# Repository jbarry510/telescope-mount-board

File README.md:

# telescope-mount-board
Printed circuit board design for a stepper motor driven telescope mount.

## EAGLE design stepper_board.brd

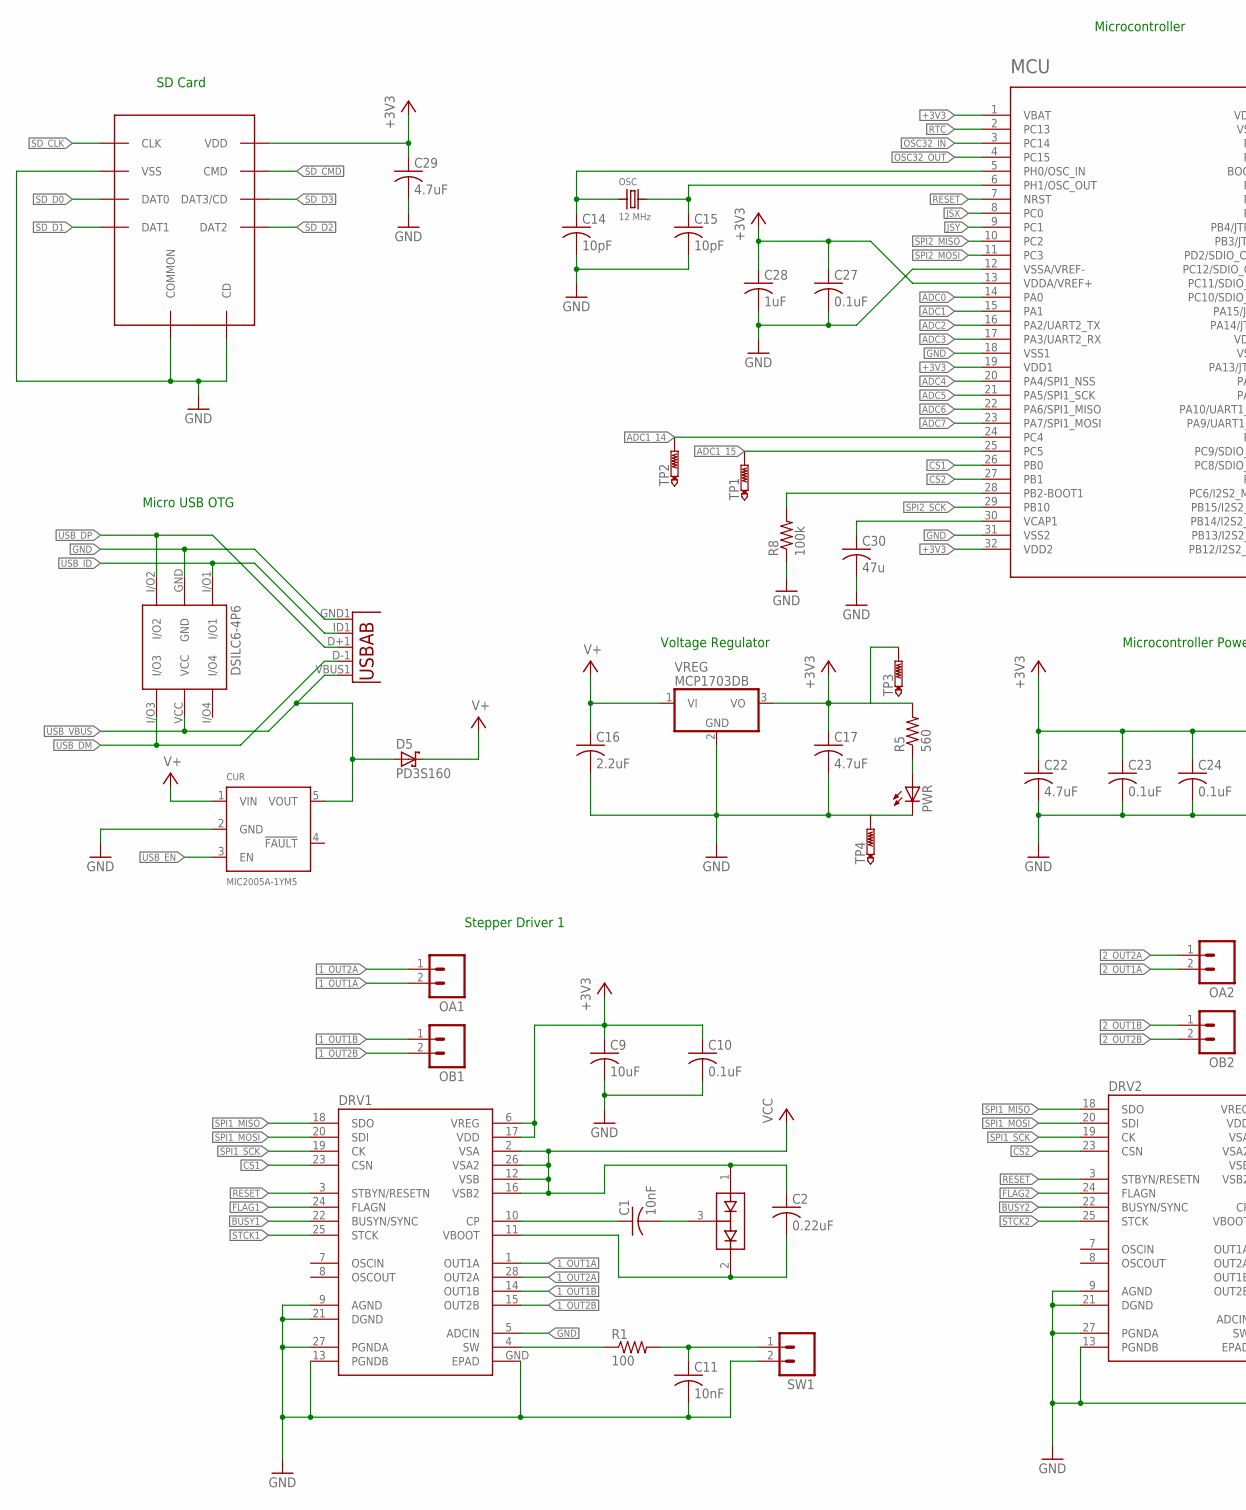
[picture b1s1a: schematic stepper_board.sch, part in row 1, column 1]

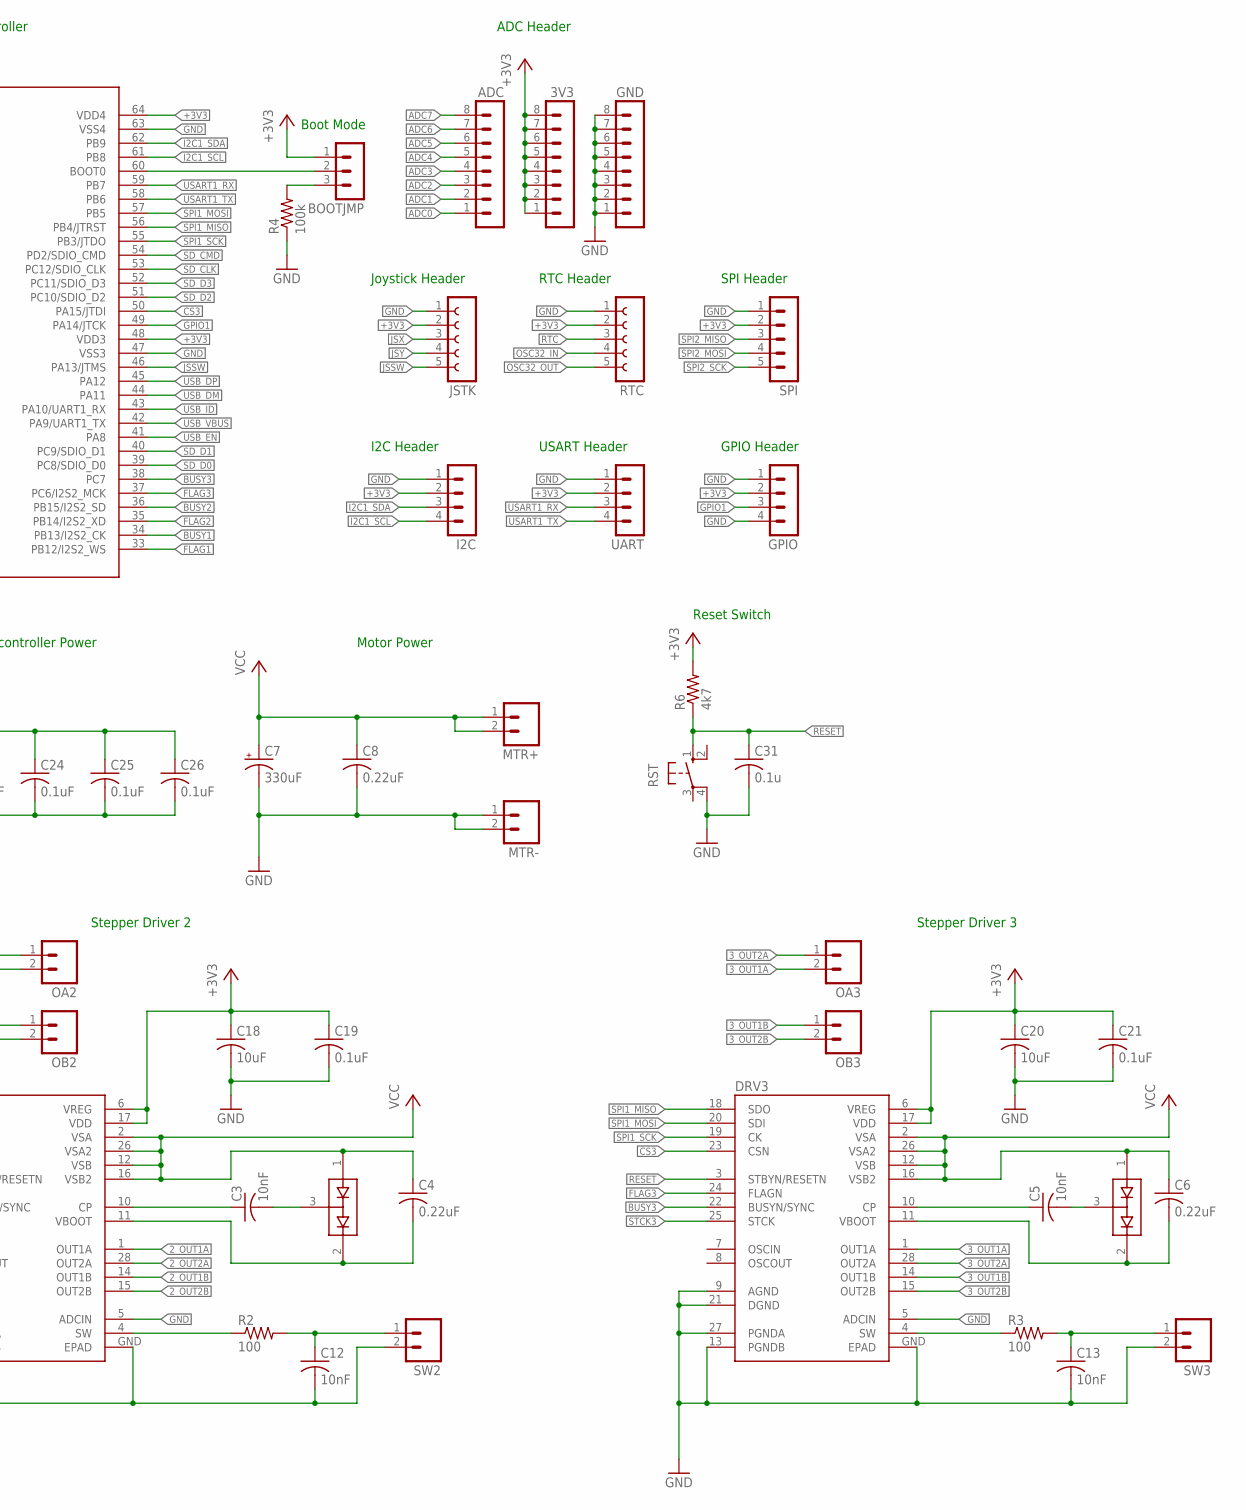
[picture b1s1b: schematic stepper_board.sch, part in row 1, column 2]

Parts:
3V3: MA08-1
ADC: MA08-1
BOOTJMP: MA03-1
C1, C3, C5, C11, C12, C13: 10nF; C0805
C2, C4, C6, C8: 0.22uF; C0805
C7: 330uF; UD-10X10_NICHICON
C9, C18, C20: 10uF; C0805
C10, C19, C21, C23, C24, C25, C26, C27: 0.1uF; C0805
C14, C15: 10pF; C0805
C16: 2.2uF; C0805
C17, C22, C29: 4.7uF; C0805
C28: 1uF; C0805
C30: 47u; C0805
C31: 0.1u; C0805
CUR: MIC2005A-1YM5; SOT23-5
D1, D2, D3: BAV99; SOT23
D5: PD3S160; POWERDI323
DRV1, DRV2, DRV3: L6470; HTSSOP28-NOPAD
ESD: DSILC6-4P6; SOT-666
GND: MA08-1
GPIO: MA04-1
I2C: MA04-1
JSTK: FE05-1
MCU: STM32F411RE; TQFP64
MICROSD: SCHA5B0200
MTR+: M02; 02P
MTR-: M02; 02P
OA1, OA2, OA3: M02; 02P
OB1, OB2, OB3: M02; 02P
OSC: 12 MHz; 3.2X2.5MM
PWR: LEDCHIP-LED0805; CHIP-LED0805
R1, R2, R3: 100; R0805
R4, R8: 100k; R0805
R5: 560; R0805
R6: 4k7; R0805
RST: 10-XX; B3F-10XX
RTC: FE05-1
SPI: MA05-1
SW1, SW2, SW3: M02; 02P
TP1, TP2, TP3, TP4: PTR1B1,27; B1,27
UART: MA04-1
USB: USB""; USB-MICRO-SMD
VREG: MCP1703DB; SOT223

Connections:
1_OUT1A: DRV1.1 (OUT1A), OA1.2
1_OUT1B: DRV1.14 (OUT1B), OB1.1
1_OUT2A: DRV1.28 (OUT2A), OA1.1
1_OUT2B: DRV1.15 (OUT2B), OB1.2
2_OUT1A: DRV2.1 (OUT1A), OA2.2
2_OUT1B: DRV2.14 (OUT1B), OB2.1
2_OUT2A: DRV2.28 (OUT2A), OA2.1
2_OUT2B: DRV2.15 (OUT2B), OB2.2
3_OUT1A: DRV3.1 (OUT1A), OA3.2
3_OUT1B: DRV3.14 (OUT1B), OB3.1
3_OUT2A: DRV3.28 (OUT2A), OA3.1
3_OUT2B: DRV3.15 (OUT2B), OB3.2
+3V3: 3V3.1, 3V3.2, 3V3.3, 3V3.4, 3V3.5, 3V3.6, 3V3.7, 3V3.8, BOOTJMP.1, C9.1, C10.1, C17.1, C18.1, C19.1, C20.1, C21.1, C22.1, C23.1, C24.1, C25.1, C26.1, C27.1, C28.1, C29.1, DRV1.6 (VREG), DRV1.17 (VDD), DRV2.6 (VREG), DRV2.17 (VDD), DRV3.6 (VREG), DRV3.17 (VDD), GPIO.2, I2C.2, JSTK.2, MCU.1 (VBAT), MCU.13 (VDDA/VREF+), MCU.19 (VDD1), MCU.32 (VDD2), MCU.48 (VDD3), MCU.64 (VDD4), MICROSD.VDD, R5.2, R6.2, RTC.2, SPI.2, TP3.TP, UART.2, VREG.3 (VO)
ADC0: ADC.1, MCU.14 (PA0)
ADC1: ADC.2, MCU.15 (PA1)
ADC1_14: MCU.24 (PC4), TP2.TP
ADC1_15: MCU.25 (PC5), TP1.TP
ADC2: ADC.3, MCU.16 (PA2/UART2_TX)
ADC3: ADC.4, MCU.17 (PA3/UART2_RX)
ADC4: ADC.5, MCU.20 (PA4/SPI1_NSS)
ADC5: ADC.6, MCU.21 (PA5/SPI1_SCK)
ADC6: ADC.7, MCU.22 (PA6/SPI1_MISO)
ADC7: ADC.8, MCU.23 (PA7/SPI1_MOSI)
BUSY1: DRV1.22 (BUSYN/SYNC), MCU.34 (PB13/I2S2_CK)
BUSY2: DRV2.22 (BUSYN/SYNC), MCU.36 (PB15/I2S2_SD)
BUSY3: DRV3.22 (BUSYN/SYNC), MCU.38 (PC7)
CS1: DRV1.23 (CSN), MCU.26 (PB0)
CS2: DRV2.23 (CSN), MCU.27 (PB1)
CS3: DRV3.23 (CSN), MCU.50 (PA15/JTDI)
FLAG1: DRV1.24 (FLAGN), MCU.33 (PB12/I2S2_WS)
FLAG2: DRV2.24 (FLAGN), MCU.35 (PB14/I2S2_XD)
FLAG3: DRV3.24 (FLAGN), MCU.37 (PC6/I2S2_MCK)
GND: C7.-, C8.2, C9.2, C10.2, C11.2, C12.2, C13.2, C14.2, C15.2, C16.2, C17.2, C18.2, C19.2, C20.2, C21.2, C22.2, C23.2, C24.2, C25.2, C26.2, C27.2, C28.2, C29.2, C30.2, C31.2, CUR.2 (GND), DRV1.5 (ADCIN), DRV1.9 (AGND), DRV1.13 (PGNDB), DRV1.21 (DGND), DRV1.27 (PGNDA), DRV1.GND (EPAD), DRV2.5 (ADCIN), DRV2.9 (AGND), DRV2.13 (PGNDB), DRV2.21 (DGND), DRV2.27 (PGNDA), DRV2.GND (EPAD), DRV3.5 (ADCIN), DRV3.9 (AGND), DRV3.13 (PGNDB), DRV3.21 (DGND), DRV3.27 (PGNDA), DRV3.GND (EPAD), ESD.GND, GND.1, GND.2, GND.3, GND.4, GND.5, GND.6, GND.7, GND.8, GPIO.1, GPIO.4, I2C.1, JSTK.1, MCU.12 (VSSA/VREF-), MCU.18 (VSS1), MCU.31 (VSS2), MCU.47 (VSS3), MCU.63 (VSS4), MICROSD.CD_SW (CD), MICROSD.COMMON, MICROSD.VSS, MTR-.1, MTR-.2, PWR.C, R4.1, R8.1, RST.4 (P1), RTC.1, SPI.1, SW1.2, SW2.2, SW3.2, TP4.TP, UART.1, USB.GND1 (GND), VREG.2 (GND)
GPIO1: GPIO.3, MCU.49 (PA14/JTCK)
I2C1_SCL: I2C.4, MCU.61 (PB8)
I2C1_SDA: I2C.3, MCU.62 (PB9)
JSSW: JSTK.5, MCU.46 (PA13/JTMS)
JSX: JSTK.3, MCU.8 (PC0)
JSY: JSTK.4, MCU.9 (PC1)
unnamed: C1.1, DRV1.10 (CP)
unnamed: C1.2, D1.3 (COM)
unnamed: C2.2, D1.2 (C2), DRV1.11 (VBOOT)
unnamed: C3.1, DRV2.10 (CP)
unnamed: C3.2, D2.3 (COM)
unnamed: C4.2, D2.2 (C2), DRV2.11 (VBOOT)
unnamed: DRV1.4 (SW), R1.1
unnamed: C5.1, DRV3.10 (CP)
unnamed: C5.2, D3.3 (COM)
unnamed: C6.2, D3.2 (C2), DRV3.11 (VBOOT)
unnamed: C11.1, R1.2, SW1.1
unnamed: DRV2.4 (SW), R2.1
unnamed: C12.1, R2.2, SW2.1
unnamed: DRV3.4 (SW), R3.1
unnamed: C13.1, R3.2, SW3.1
unnamed: C14.1, MCU.5 (PH0/OSC_IN), OSC.1
unnamed: C15.1, MCU.6 (PH1/OSC_OUT), OSC.3 (2)
unnamed: BOOTJMP.2, MCU.60 (BOOT0)
unnamed: BOOTJMP.3, R4.2
unnamed: PWR.A, R5.1
unnamed: C30.1, MCU.30 (VCAP1)
unnamed: MCU.28 (PB2-BOOT1), R8.2
OSC32_IN: MCU.3 (PC14), RTC.4
OSC32_OUT: MCU.4 (PC15), RTC.5
RESET: C31.1, DRV1.3 (STBYN/RESETN), DRV2.3 (STBYN/RESETN), DRV3.3 (STBYN/RESETN), MCU.7 (NRST), R6.1, RST.1 (S)
RTC: MCU.2 (PC13), RTC.3
SD_CLK: MCU.53 (PC12/SDIO_CLK), MICROSD.CLK
SD_CMD: MCU.54 (PD2/SDIO_CMD), MICROSD.CMD
SD_D0: MCU.39 (PC8/SDIO_D0), MICROSD.DAT0
SD_D1: MCU.40 (PC9/SDIO_D1), MICROSD.DAT1
SD_D2: MCU.51 (PC10/SDIO_D2), MICROSD.DAT2
SD_D3: MCU.52 (PC11/SDIO_D3), MICROSD.DAT3/CD
SPI1_MISO: DRV1.18 (SDO), DRV2.18 (SDO), DRV3.18 (SDO), MCU.56 (PB4/JTRST)
SPI1_MOSI: DRV1.20 (SDI), DRV2.20 (SDI), DRV3.20 (SDI), MCU.57 (PB5)
SPI1_SCK: DRV1.19 (CK), DRV2.19 (CK), DRV3.19 (CK), MCU.55 (PB3/JTDO)
SPI2_MISO: MCU.10 (PC2), SPI.3
SPI2_MOSI: MCU.11 (PC3), SPI.4
SPI2_SCK: MCU.29 (PB10), SPI.5
STCK1: DRV1.25 (STCK)
STCK2: DRV2.25 (STCK)
STCK3: DRV3.25 (STCK)
USART1_RX: MCU.59 (PB7), UART.3
USART1_TX: MCU.58 (PB6), UART.4
USB_DM: ESD.I/O3, MCU.44 (PA11), USB.D-1 (D-)
USB_DP: ESD.I/O2, MCU.45 (PA12), USB.D+1 (D+)
USB_EN: CUR.3 (EN), MCU.41 (PA8)
USB_ID: ESD.I/O1, MCU.43 (PA10/UART1_RX), USB.ID1 (USBID)
USB_VBUS: CUR.5 (VOUT), D5.A, ESD.VCC, MCU.42 (PA9/UART1_TX), USB.VBUS1 (VBUS)
V+: C16.1, CUR.1 (VIN), D5.C, VREG.1 (VI)
VCC: C2.1, C4.1, C6.1, C7.+, C8.1, D1.1 (A1), D2.1 (A1), D3.1 (A1), DRV1.2 (VSA), DRV1.12 (VSB), DRV1.16 (VSB2), DRV1.26 (VSA2), DRV2.2 (VSA), DRV2.12 (VSB), DRV2.16 (VSB2), DRV2.26 (VSA2), DRV3.2 (VSA), DRV3.12 (VSB), DRV3.16 (VSB2), DRV3.26 (VSA2), MTR+.1, MTR+.2

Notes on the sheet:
Motor Power
Voltage Regulator
SD Card
Stepper Driver 1
Stepper Driver 2
Stepper Driver 3
Micro USB OTG
Microcontroller
Microcontroller Power
ADC Header
Joystick Header
RTC Header
I2C Header
USART Header
Boot Mode
GPIO Header
SPI Header
Reset Switch

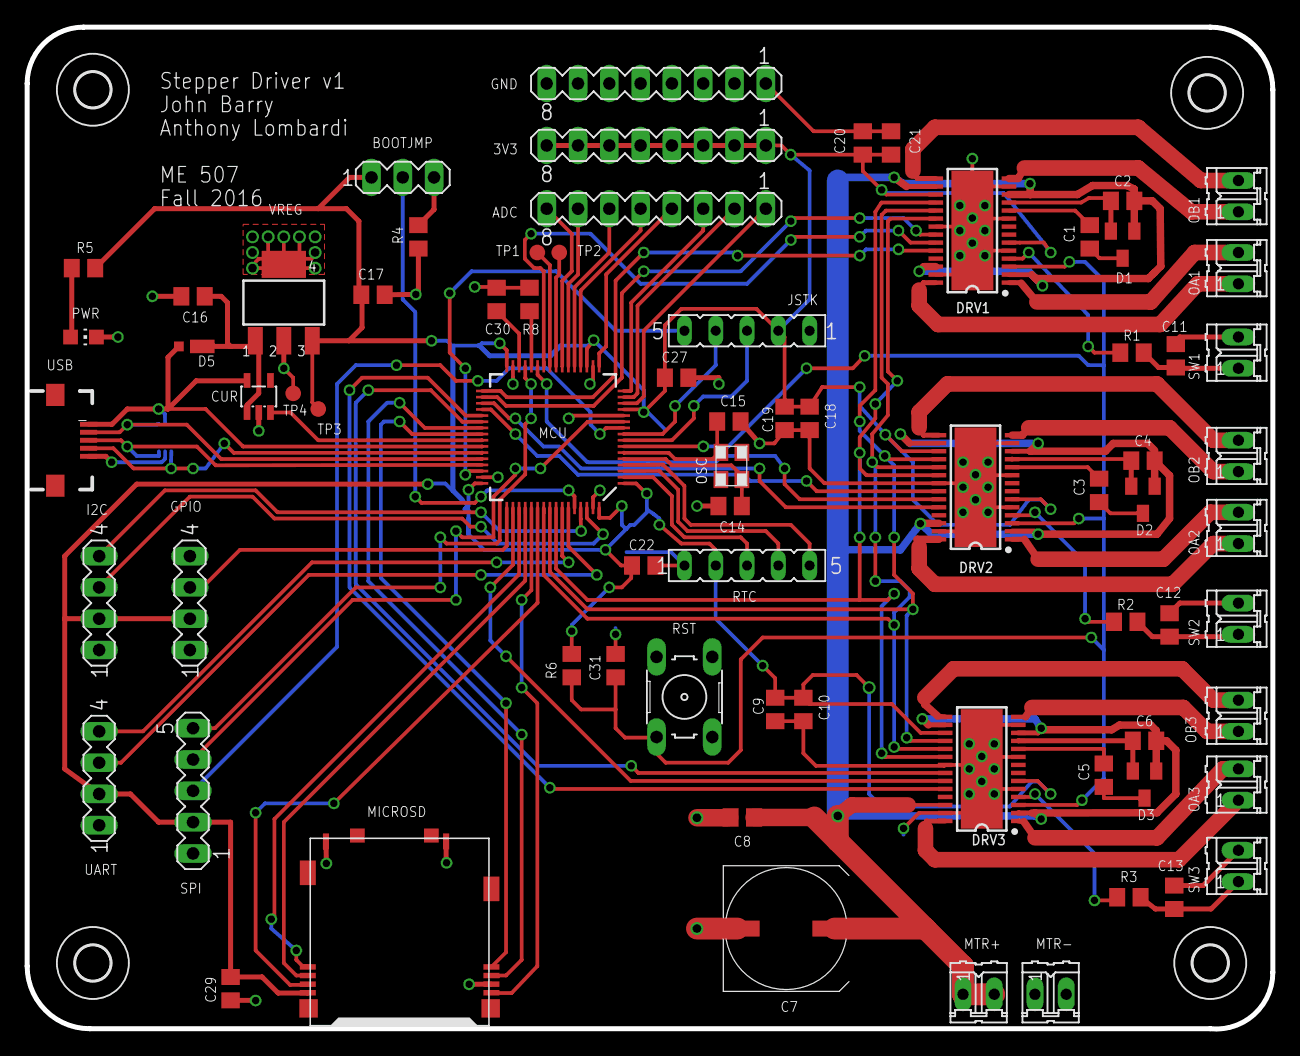
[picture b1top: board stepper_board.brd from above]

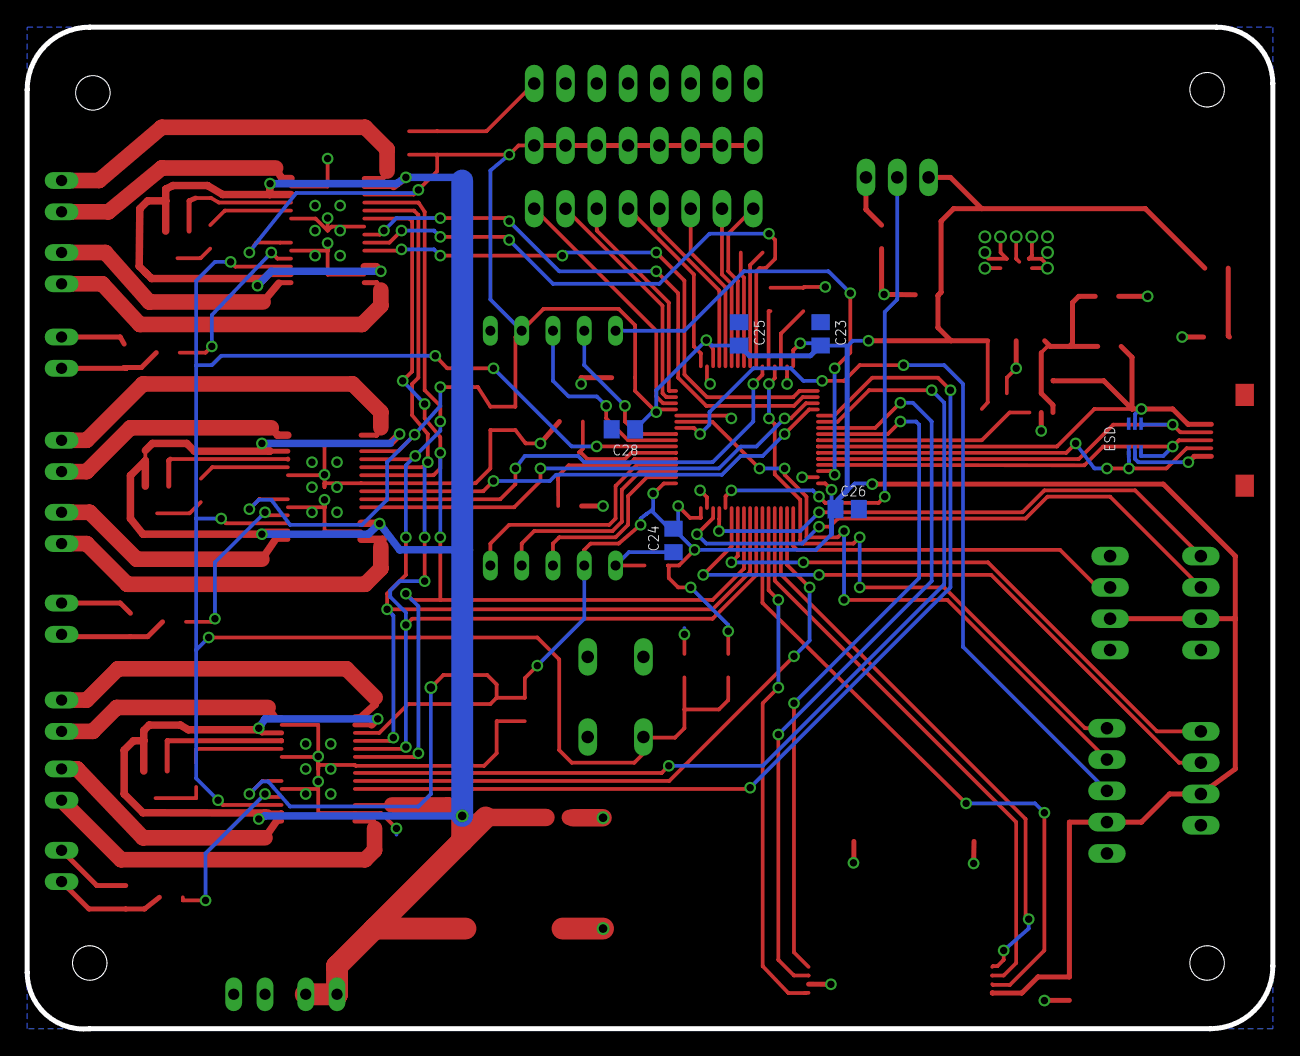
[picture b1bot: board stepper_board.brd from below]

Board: 2 copper layers, 101.1 x 81.3 mm, 83 parts (6 on the bottom side), 86 nets.

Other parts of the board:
U$2, U$3, U$4, U$5: 2,8

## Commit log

2016-10-14 Inital commit for ME 507 project board
2016-10-14 Added .gitignore file for Eagle folder
2016-10-14 Removed TI DRV8825 from schematic and remove its library
2016-10-15 Removed unnecessary library and added STM32F411RE to DigitalIC.lbr
2016-10-15 Added correct MCU (STM32F411RE), started wiring MCU to drivers, and added datasheets
2016-10-18 Added some grounding connections to the driver chips on schematic
2016-10-24 Added more connections to stepper drivers on schematic
2016-10-27 Added all the stuffs
2016-10-28 Added datasheet and libraries for components. Added MicroSD, MicroUSB, and power regulation to microcontroller schematic.
2016-10-28 Created board file, added ground plane and moved components to board trying to match schematic
2016-10-31 Added ESD Protection and STM documentation
2016-11-02 Tried to start unraveling the rats' nest.
2016-11-02 More wiring in progress
2016-11-03 Changed L6470 package footprint, added chip select pins to drivers, started routing
2016-11-03 Routed tons o' stuff
2016-11-03 Finished routing! Also added test points.
2016-11-04 Added reset switch, thermal pad vias, cleaned up some traces, and fixed usb footprint
2016-11-04 Modified silkscreen layer to make labels clear
2016-11-04 Small changes to silkscreen
2016-11-05 Fixed small airwires that were not routed
2016-11-05 Move some silkscreen labels
2016-11-05 Changed value of motor blocking cap
2016-11-05 Made the power traces on the drivers slightly bigger
2016-11-05 More tracing beefyness
2016-11-05 Removed solder mask on top layer under motor driver chips
2016-11-05 Slight change to a capacitor value
2016-12-01 Added license

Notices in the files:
parts and their libraries:
DiscreteSemi: Licensing: CC v3.0 Share-Alike You are welcome to use this library for commercial purposes.
DigitalIC: Licensing: Creative Commons ShareAlike 4.0 International - https://creativecommons.org/licenses/by-sa/4.0
